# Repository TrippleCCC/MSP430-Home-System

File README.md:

# ELEC 327 Final Project: Home Hub

A flutter app and msp430 for a simple home monitoring system

## Devleopment
### Preequisites
In order to develop this app you need to donwload Flutter and Code Composer Studio.
The root of this repo can be used for the project root of the flutter app.
The folder msp430_code can be used for the root of the Code Composer project.

### Flutter
The library used for bluetooth communication is not up to date with Flutters current
null safety standard. Therefore to run the app use the following command

```bash
flutter run --no-sound-null-safety
```

This will allow you to run the app without checking for null safety.

## Presentation Links
Presentation link [here](https://youtu.be/QDikoYCsCTo)
Demo Link [here](https://youtu.be/2Ma--qm9nqg)

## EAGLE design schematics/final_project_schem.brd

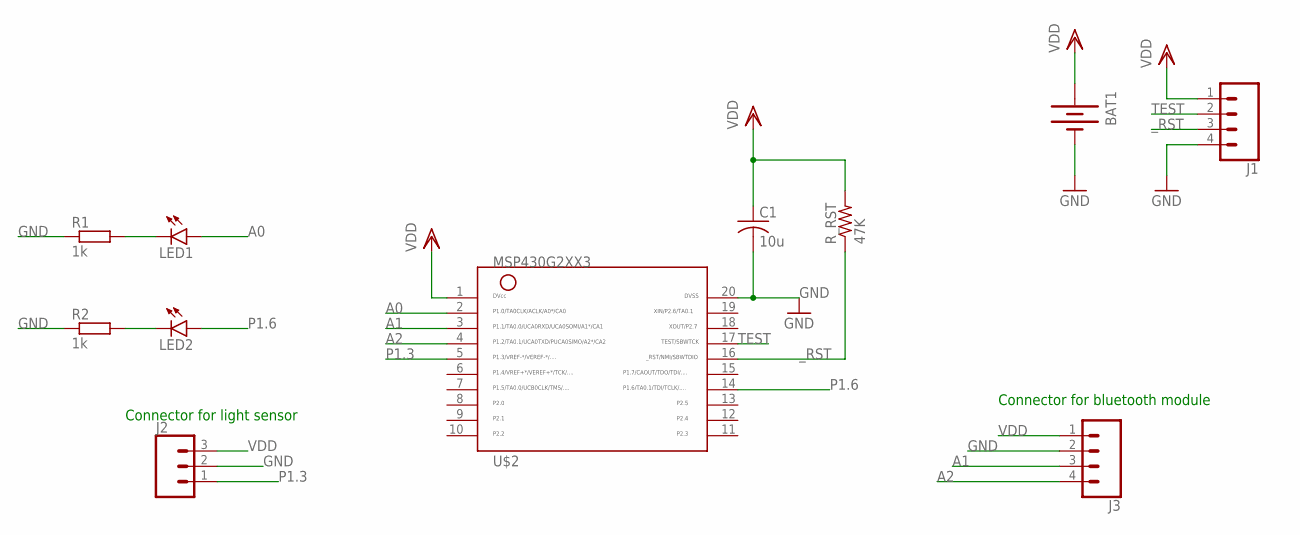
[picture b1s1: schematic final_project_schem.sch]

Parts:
BAT1: BATTERYBU2032SM; BU2032SM
C1: 10u; C1206
J1, J3: CONN_04LOCK; 1X04_LOCK
J2: CONN_03LOCK; 1X03_LOCK
LED1, LED2: LEDCHIPLED_0805; CHIPLED_0805
R1, R2: 1k; R0603
R_RST: 47K; R1206
U$2: MSP430G2XX3TSSOP; PW20

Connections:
A0: LED1.A, U$2.2
A1: J3.3, U$2.3
A2: J3.4, U$2.4
GND: BAT1.P$2 (-), C1.2, J1.4, J2.2, J3.2, R1.1, R2.1, U$2.20
unnamed: LED1.C, R1.2
unnamed: LED2.C, R2.2
P1.3: J2.1, U$2.5
P1.6: LED2.A, U$2.14
TEST: J1.2, U$2.17
VDD: BAT1.P$1 (+), C1.1, J1.1, J2.3, J3.1, R_RST.2, U$2.1
_RST: J1.3, R_RST.1, U$2.16

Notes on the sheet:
Connector for bluetooth module
Connector for light sensor

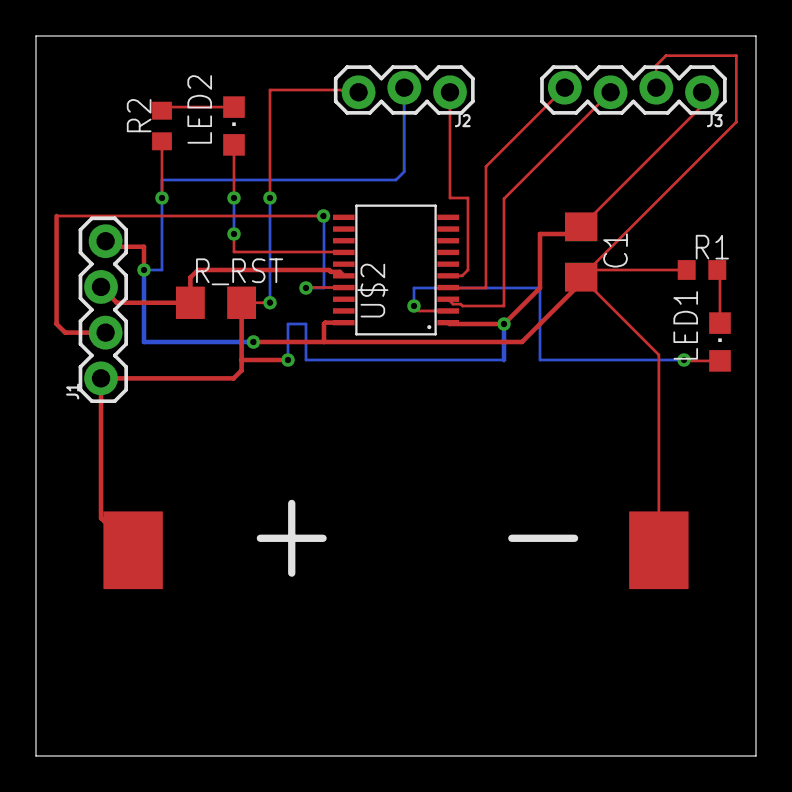
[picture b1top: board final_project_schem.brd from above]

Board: 2 copper layers, 40.0 x 40.0 mm, 11 parts (0 on the bottom side), 11 nets.

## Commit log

2021-05-11 Typo
2021-05-11 Add report
2021-05-11 Add links to presentation and demo videos
2021-05-12 Add schematics

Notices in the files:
parts and their libraries:
SparkFun-Connectors: Licensing: Creative Commons ShareAlike 4.0 International - https://creativecommons.org/licenses/by-sa/4.0
